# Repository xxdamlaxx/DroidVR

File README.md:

# 🥽 DroidVR

A DIY VR controller ecosystem — open-source hardware and firmware for SteamVR-compatible motion controllers.

---

## License

DroidVR is available under a **dual license** model. Pick whichever fits your use case.

### Option 1 — Free & Open (Attribution Required)

Use, modify, distribute, and sell DroidVR for free, as long as you provide clear and visible attribution in your project's documentation, about page, and repository.

**Required attribution:**

> Built with **DroidVR** by [xxdamlaxx](https://github.com/xxdamlaxx)

See [`LICENSE.md`](LICENSE.md) for full terms.

### Option 2 — Commercial License (No Attribution)

If you prefer not to include attribution, you can purchase a commercial license:

| Tier | Monthly Fee |
|---|---|
| Public / Open-Source Development | $500 / month |
| Private / Closed-Source Development | $5,000 / month |

- Prices may be adjusted at the end of each calendar year.
- No refunds.

See [`LICENSE-COMMERCIAL.md`](LICENSE-COMMERCIAL.md) for full terms.

---

## Contact

For commercial licensing inquiries, reach out via [GitHub](https://github.com/xxdamlaxx) or email *(coming soon)*.

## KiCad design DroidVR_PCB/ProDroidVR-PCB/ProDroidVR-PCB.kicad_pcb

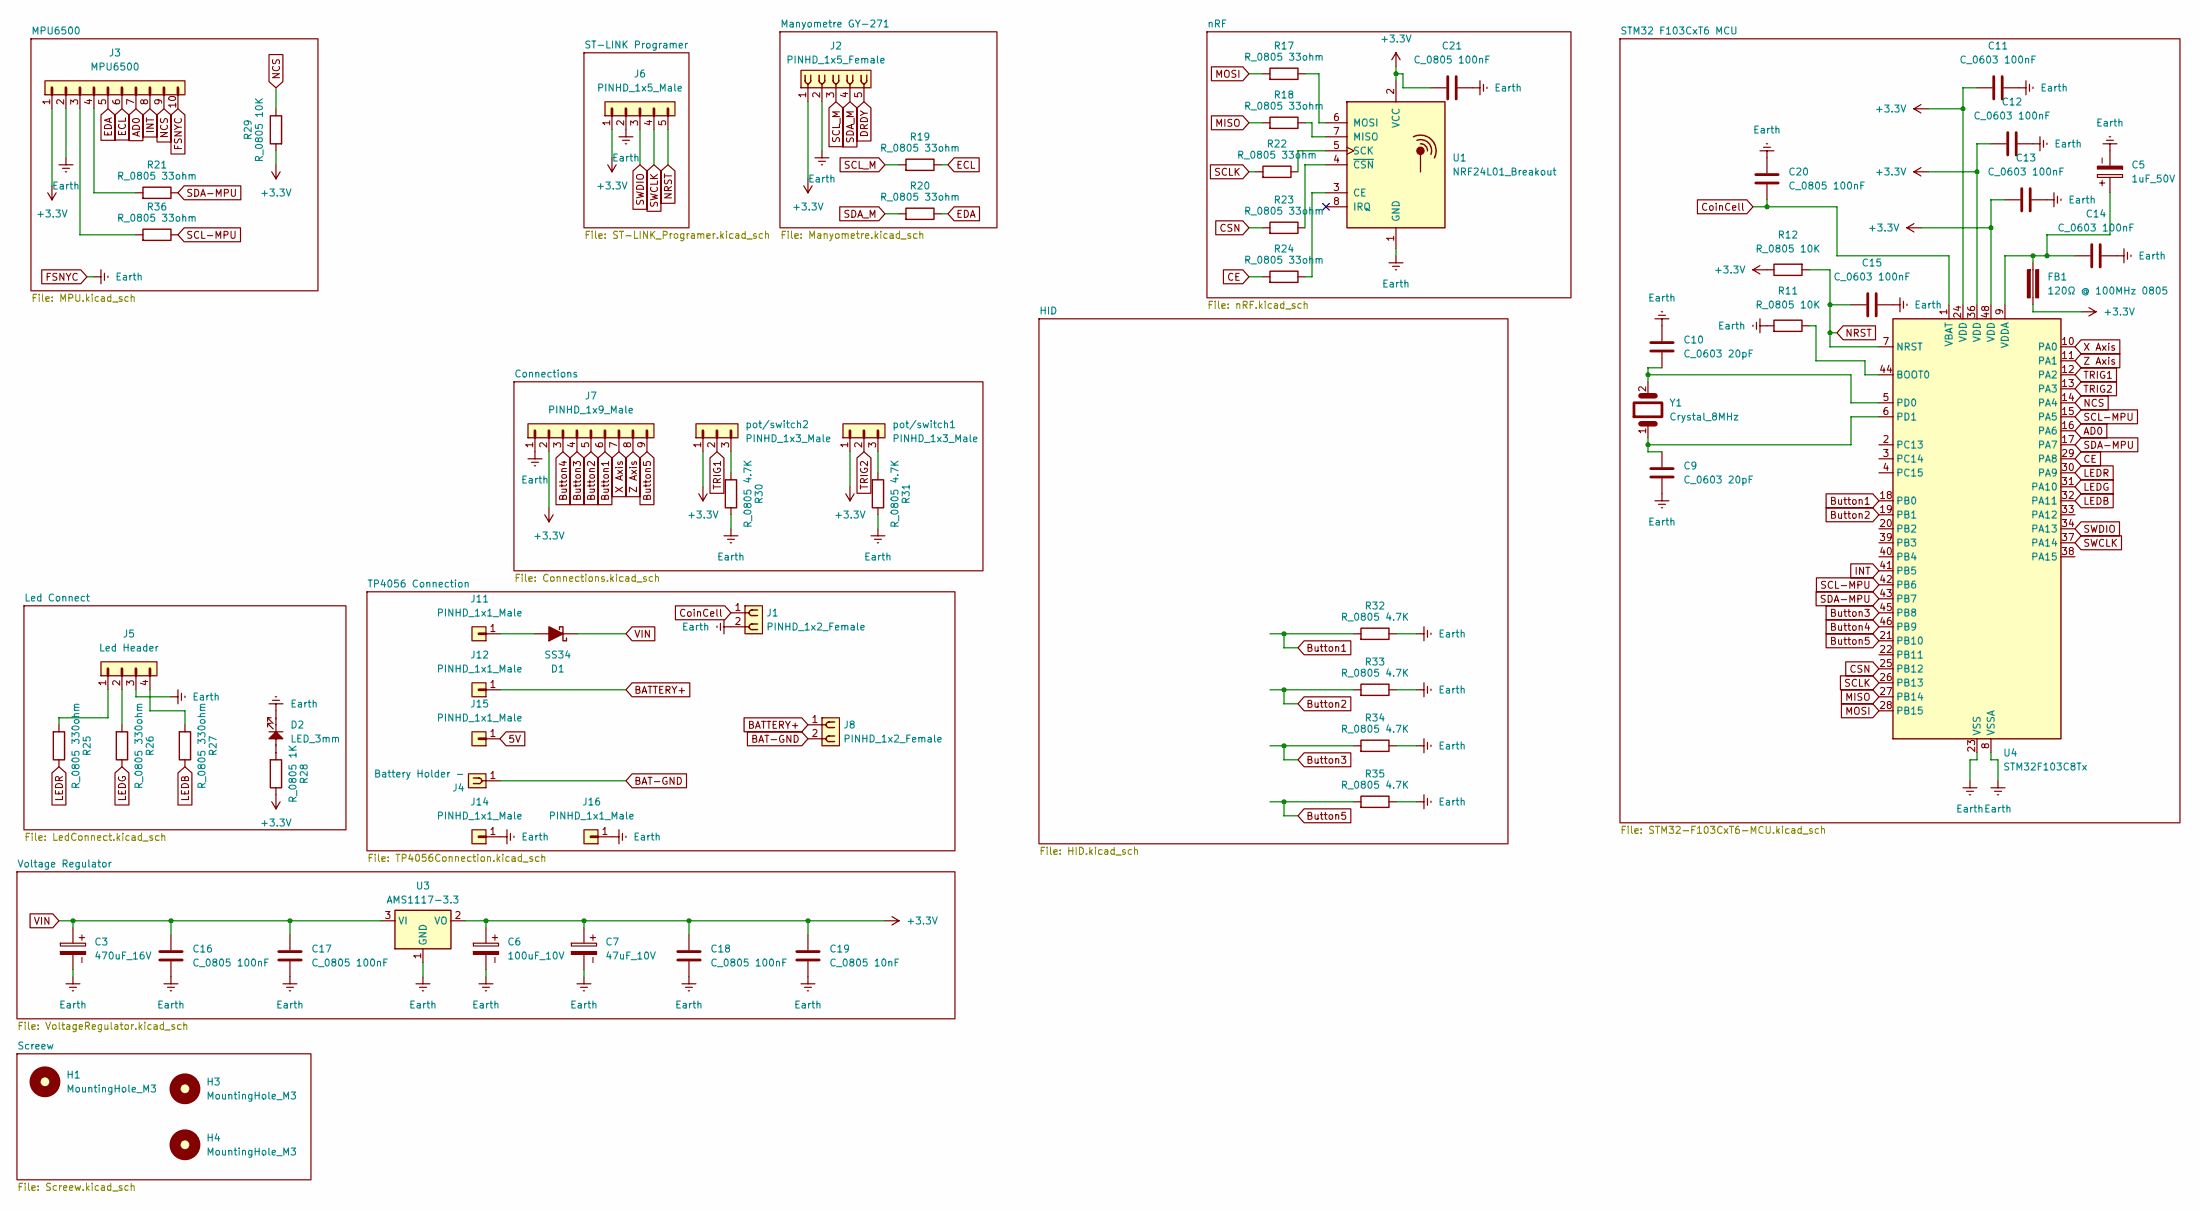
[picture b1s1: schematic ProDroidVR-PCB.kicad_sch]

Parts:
C3: 470uF_16V; CP_Radial_D8.0mm_P3.50mm
C5: 1uF_50V; CP_Radial_D4.0mm_P1.50mm
C6: 100uF_10V; CP_Radial_D5.0mm_P2.00mm
C7: 47uF_10V; CP_Radial_D4.0mm_P1.50mm
C9, C10: C_0603 20pF; C_0603_1608Metric
C11, C12, C13, C14, C15: C_0603 100nF; C_0603_1608Metric
C16, C17, C18, C20, C21: C_0805 100nF; C_0805_2012Metric
C19: C_0805 10nF; C_0805_2012Metric
D1: SS34; D_SMC
D2: LED_3mm; LED_D3.0mm
FB1: 120Ω @ 100MHz 0805; R_0805_2012Metric
H1, H3, H4: MountingHole_M3; MountingHole_3.2mm_M3
J1: PINHD_1x2_Female; BatteryHolder_MYOUNG_BS-07-A1BJ001_CR2032
J2: PINHD_1x5_Female; PinSocket_1x05_P2.54mm_Vertical
J3: MPU6500; PinHeader_1x10_P2.54mm_Vertical
J4: Battery Holder -; TestPoint_THTPad_2.0x2.0mm_Drill1.0mm
J5: Led Header; PinHeader_1x04_P2.54mm_Vertical
J6: PINHD_1x5_Male; PinHeader_1x05_P2.54mm_Vertical
J7: PINHD_1x9_Male; PinHeader_1x09_P2.54mm_Vertical
J8: PINHD_1x2_Female; BatteryHolder_MPD_BH-18650-PC2
J11, J12, J14, J15, J16: PINHD_1x1_Male; TestPoint_THTPad_2.0x2.0mm_Drill1.0mm
R11, R12, R29: R_0805 10K; R_0805_2012Metric
R17, R18, R19, R20, R21, R22, R23, R24, R36: R_0805 33ohm; R_0805_2012Metric
R25, R26, R27: R_0805 330ohm; R_0805_2012Metric
R28: R_0805 1K; R_0805_2012Metric
R30, R31, R32, R33, R34, R35: R_0805 4.7K; R_0805_2012Metric
U1: NRF24L01_Breakout; nRF24L01_Breakout
U3: AMS1117-3.3; SOT-223-3_TabPin2
U4: STM32F103C8Tx; LQFP-48_7x7mm_P0.5mm
Y1: Crystal_8MHz; Crystal_HC49-4H_Vertical
pot/switch1, pot/switch2: PINHD_1x3_Male; PinHeader_1x03_P2.54mm_Vertical

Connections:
5V: J15.1
+3.3V: C6.1, C7.1, C11.1, C12.1, C13.1, C18.2, C19.2, C21.2, FB1.2, J2.1, J3.1, J6.1, J7.2, R12.2, R28.2, R29.1, U1.2 (VCC), U3.2 (VO), U4.24 (VDD), U4.36 (VDD), U4.48 (VDD), pot/switch1.1, pot/switch2.1
AD0: J3.7, U4.16 (PA6)
BAT-GND: J4.1, J8.2
BATTERY+: J8.1, J12.1
Button1: J7.6, R32.1, U4.18 (PB0)
Button2: J7.5, R33.1, U4.19 (PB1)
Button3: J7.4, R34.1, U4.45 (PB8)
Button4: J7.3, U4.46 (PB9)
Button5: J7.9, R35.1, U4.21 (PB10)
CE: R24.1, U4.29 (PA8)
CSN: R23.1, U4.25 (PB12)
CoinCell: C20.2, J1.1, U4.1 (VBAT)
DRDY: J2.5
ECL: J3.6, R19.2
EDA: J3.5, R20.2
FSNYC: C3.2, C5.2, C6.2, C7.2, C9.2, C10.1, C11.2, C12.2, C13.2, C14.2, C15.2, C16.1, C17.1, C18.1, C19.1, C20.1, C21.1, D2.1, J1.2, J2.2, J3.2, J3.10, J5.3, J6.2, J7.1, J14.1, J16.1, R11.1, R30.2, R31.2, R32.2, R33.2, R34.2, R35.2, U1.1 (GND), U3.1 (GND), U4.8 (VSSA), U4.23 (VSS), U4.35 (VSS), U4.47 (VSS)
INT: J3.8, U4.41 (PB5)
LEDB: R27.2, U4.32 (PA11)
LEDG: R26.2, U4.31 (PA10)
LEDR: R25.2, U4.30 (PA9)
MISO: R18.1, U4.27 (PB14)
MOSI: R17.1, U4.28 (PB15)
NCS: J3.9, R29.2, U4.14 (PA4)
NRST: C15.1, J6.5, R12.1, U4.7 (NRST)
unnamed: D1.2 (A), J11.1
unnamed: D2.2, R28.1
unnamed: J3.3, R36.1
unnamed: J3.4, R21.1
unnamed: J5.1, R25.1
unnamed: J5.2, R26.1
unnamed: J5.4, R27.1
unnamed: R30.1, pot/switch2.3
unnamed: R31.1, pot/switch1.3
unnamed: R24.2, U1.3 (CE)
unnamed: R18.2, U1.7 (MISO)
unnamed: R17.2, U1.6 (MOSI)
unnamed: R22.2, U1.5 (SCK)
unnamed: R23.2, U1.4 (~CSN)
unnamed: R11.2, U4.44 (BOOT0)
unnamed: C10.2, U4.5 (PD0), Y1.2
unnamed: C9.1, U4.6 (PD1), Y1.1
unnamed: C5.1, C14.1, FB1.1, U4.9 (VDDA)
SCL-MPU: R36.2, U4.15 (PA5), U4.42 (PB6)
SCLK: R22.1, U4.26 (PB13)
SCL_M: J2.3, R19.1
SDA-MPU: R21.2, U4.17 (PA7), U4.43 (PB7)
SDA_M: J2.4, R20.1
SWCLK: J6.4, U4.37 (PA14)
SWDIO: J6.3, U4.34 (PA13)
TRIG1: U4.12 (PA2), pot/switch2.2
TRIG2: U4.13 (PA3), pot/switch1.2
VIN: C3.1, C16.2, C17.2, D1.1 (K), U3.3 (VI)
X Axis: J7.7, U4.10 (PA0)
Z Axis: J7.8, U4.11 (PA1)

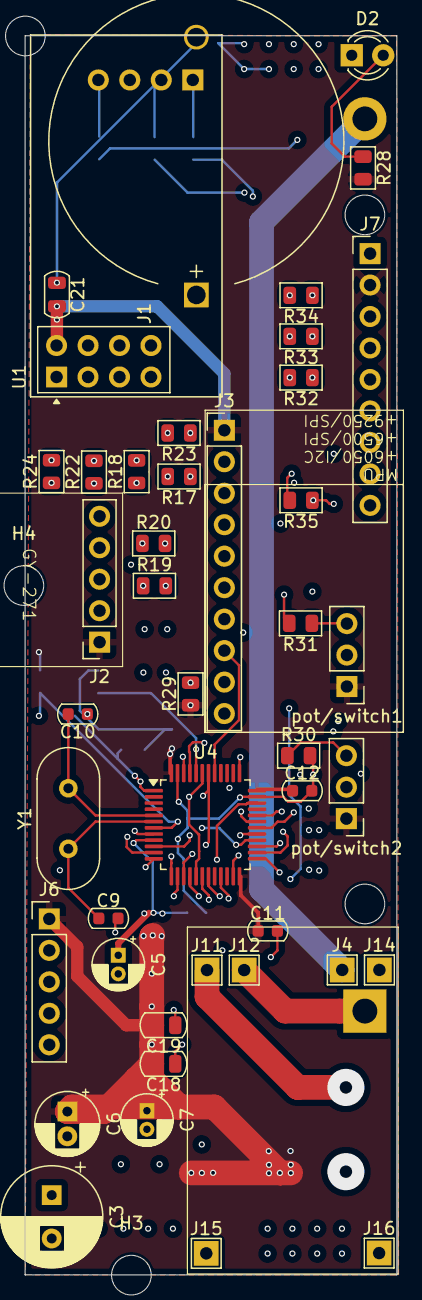
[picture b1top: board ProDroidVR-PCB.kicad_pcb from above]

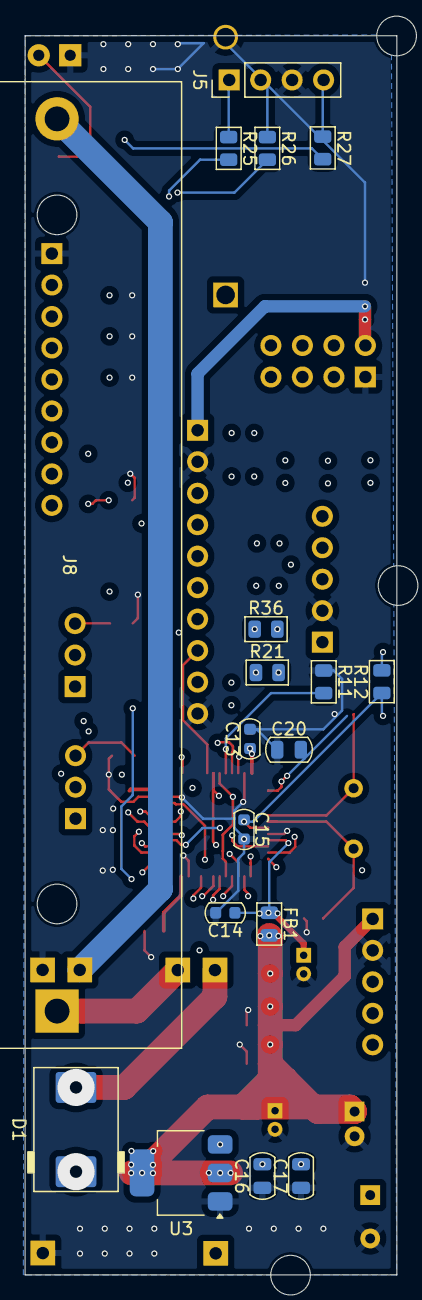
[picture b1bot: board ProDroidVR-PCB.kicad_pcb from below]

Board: 4 copper layers, 30.0 x 100.0 mm, 64 parts (18 on the bottom side), 53 nets.

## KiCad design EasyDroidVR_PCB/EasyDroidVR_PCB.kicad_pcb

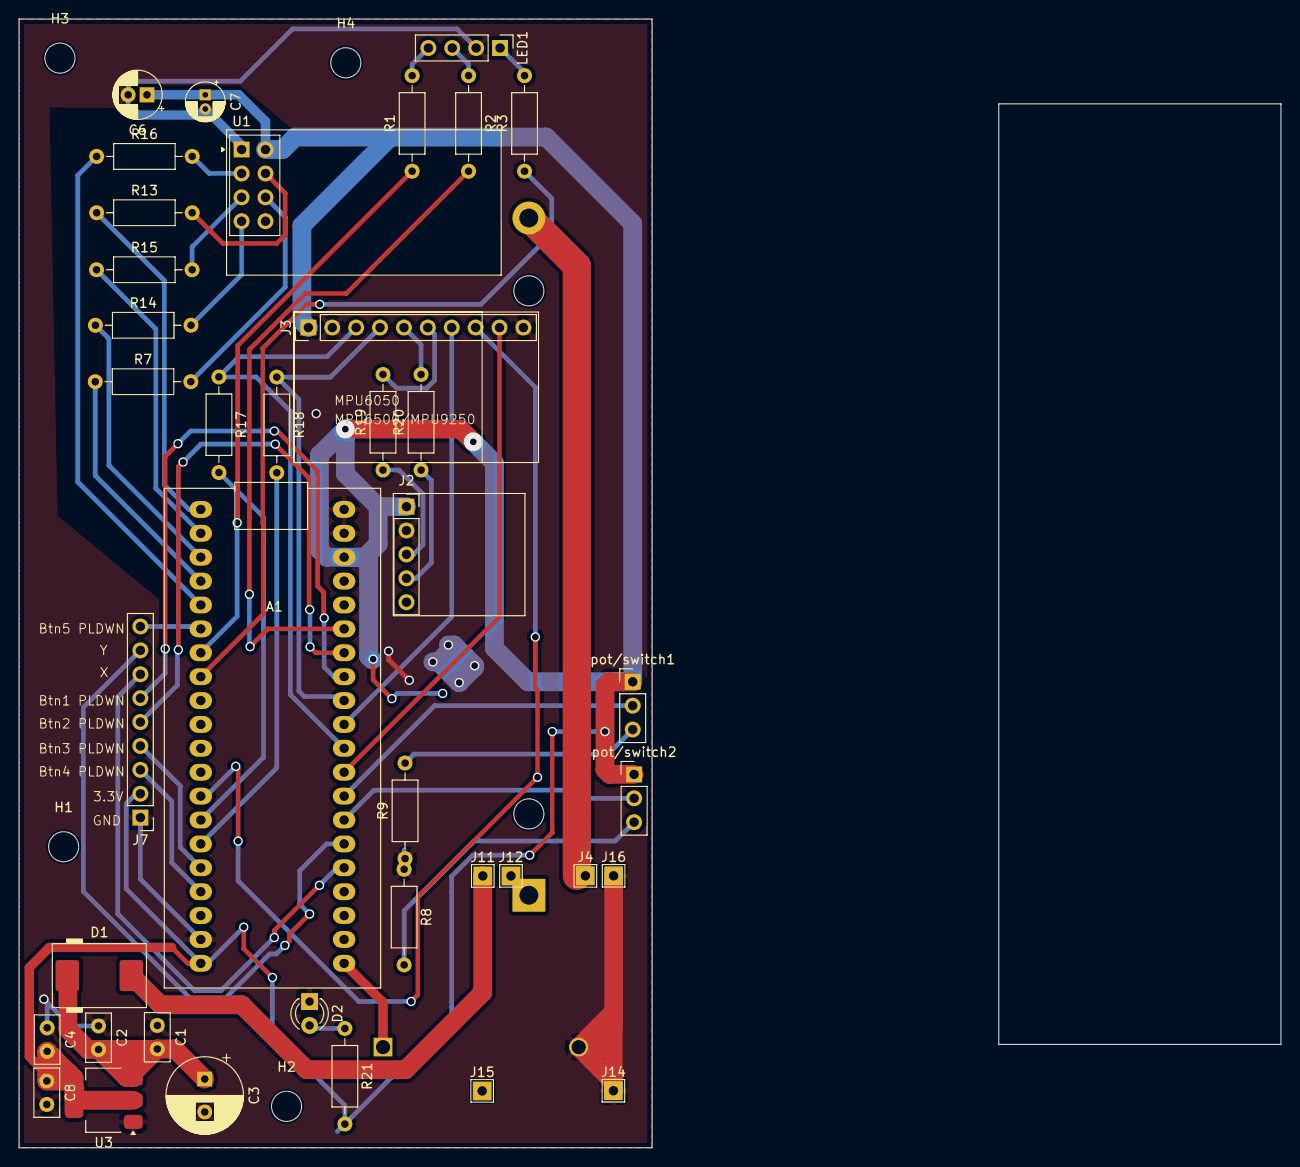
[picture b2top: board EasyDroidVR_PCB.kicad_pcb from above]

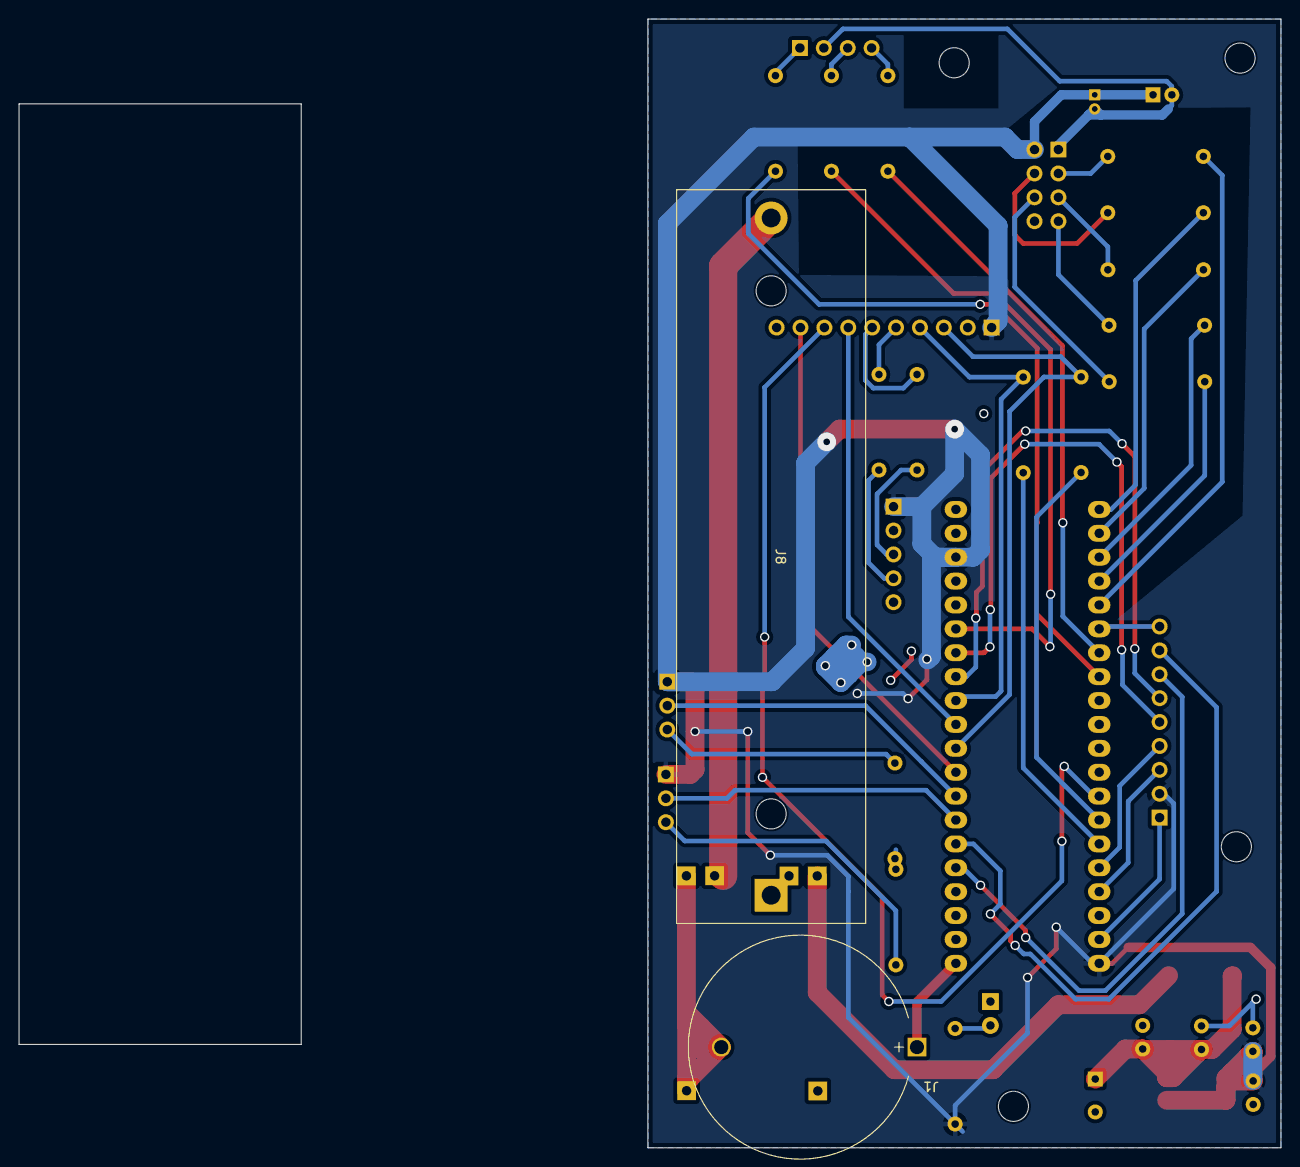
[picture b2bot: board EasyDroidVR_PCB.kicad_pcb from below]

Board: 2 copper layers, 67.3 x 120.0 mm, 45 parts (2 on the bottom side), 46 nets.

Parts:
A1: STM32_Blue_Pill_DevBoard
C1, C2, C4: 100nF_Ceramic; C_Disc_D5.0mm_W2.5mm_P2.50mm
C3: 470uF_16V; CP_Radial_D8.0mm_P3.50mm
C6: 100uF_10V; CP_Radial_D5.0mm_P2.00mm
C7: 47uF_10V; CP_Radial_D4.0mm_P1.50mm
C8: 10nF_Ceramic; C_Disc_D5.0mm_W2.5mm_P2.50mm
D1: SS34; D_SMC
D2: LED_3mm; LED_D3.0mm
H1, H2, H3, H4: MountingHole_M3; MountingHole_3.2mm_M3
J1: PINHD_1x2_Female; BatteryHolder_MYOUNG_BS-07-A1BJ001_CR2032
J2: PINHD_1x5_Female; PinSocket_1x05_P2.54mm_Vertical
J3: MPU6500; PinHeader_1x10_P2.54mm_Vertical
J4: Battery Holder -; TestPoint_THTPad_2.0x2.0mm_Drill1.0mm
J7: PINHD_1x9_Male; PinHeader_1x09_P2.54mm_Vertical
J8: PINHD_1x2_Female; BatteryHolder_MPD_BH-18650-PC2
J11, J12, J14, J15, J16: PINHD_1x1_Male; TestPoint_THTPad_2.0x2.0mm_Drill1.0mm
LED1: LED_5mm_RGB_Kcom_BKRG; PinHeader_1x04_P2.54mm_Vertical
R1, R2, R3: 330ohm; R_Axial_DIN0207_L6.3mm_D2.5mm_P10.16mm_Horizontal
R7, R13, R14, R15, R16, R17, R18, R19, R20: 33ohm; R_Axial_DIN0207_L6.3mm_D2.5mm_P10.16mm_Horizontal
R8, R9: 4.7k; R_Axial_DIN0207_L6.3mm_D2.5mm_P10.16mm_Horizontal
R21: 1k; R_Axial_DIN0207_L6.3mm_D2.5mm_P10.16mm_Horizontal
U1: NRF24L01_Breakout; nRF24L01_Breakout
U3: AMS1117-3.3; SOT-223-3_TabPin2
pot/switch1, pot/switch2: PINHD_1x3_Male; PinHeader_1x03_P2.54mm_Vertical

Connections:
+3.3V: A1.20 (3V3), A1.38 (3V3), C4.2, C6.1, C7.1, C8.1, J2.1, J3.1, J7.2, R21.2, U1.2 (VCC), U3.2 (VO), pot/switch1.1, pot/switch2.1
AD0: A1.31 (MISO1/PA6), J3.7
BAT-GND: J4.1, J8.2
BATTERY+: J8.1, J12.1
Button1: A1.33 (PB0), J7.6
Button2: A1.34 (PB1), J7.5
Button3: A1.16 (PB8/SCL1), J7.4
Button4: A1.17 (PB9/SDA1), J7.3
Button5: A1.6 (PA9/TX1), J7.9
CE: A1.5 (PA8/CK1), R16.1
CSN: A1.1 (PB12/NSS2), R13.1
CoinCell: A1.21 (VBAT), J1.1
ECL: J3.6, R19.2
EDA: J3.5, R20.2
FSNYC: A1.19 (GND), A1.39 (GND), A1.40 (GND), C1.1, C2.1, C3.2, C4.1, C6.2, C7.2, C8.2, D2.1, J1.2, J2.2, J3.2, J3.10, J7.1, J14.1, J16.1, LED1.2 (A), R8.1, R9.1, U1.1 (GND), U3.1 (GND)
INT: A1.13 (PB5/MOSI1), J3.8
LEDB: A1.8 (PA11/~USB-), R3.1
LEDG: A1.7 (PA10/RX1), R1.1
LEDR: A1.35 (SCL2/TX3/PB10), R2.2
MISO: A1.3 (PB14/MISO2), R14.1
MOSI: A1.4 (PB15/MOSI2), R7.1
NCS: A1.29 (NSS1/PA4), J3.9
unnamed: A1.14 (PB6/SCL1/TX1), R17.2
unnamed: A1.15 (PB7/SDA1/RX1), R18.2
unnamed: D1.2 (A), J11.1
unnamed: D2.2, R21.1
unnamed: LED1.1 (B), R3.2
unnamed: LED1.4 (G), R1.2
unnamed: LED1.3 (R), R2.1
unnamed: R8.2, pot/switch2.3
unnamed: R9.2, pot/switch1.3
unnamed: R16.2, U1.3 (CE)
unnamed: R14.2, U1.7 (MISO)
unnamed: R7.2, U1.6 (MOSI)
unnamed: R15.2, U1.5 (SCK)
unnamed: R13.2, U1.4 (~CSN)
SCL: A1.30 (SCK1/PA5), J3.3, R17.1
SCLK: A1.2 (PB13/SCK2), R15.1
SCL_M: J2.3, R19.1
SDA: A1.32 (MOSI1/PA7), J3.4, R18.1
SDA_M: J2.4, R20.1
TRIG1: A1.27 (TX2/PA2), pot/switch2.2
TRIG2: A1.28 (RX2/PA3), pot/switch1.2
VIN: C1.2, C2.2, C3.1, D1.1 (K), U3.3 (VI)
X Axis: A1.25 (PA0), J7.7
Z Axis: A1.26 (PA1), J7.8

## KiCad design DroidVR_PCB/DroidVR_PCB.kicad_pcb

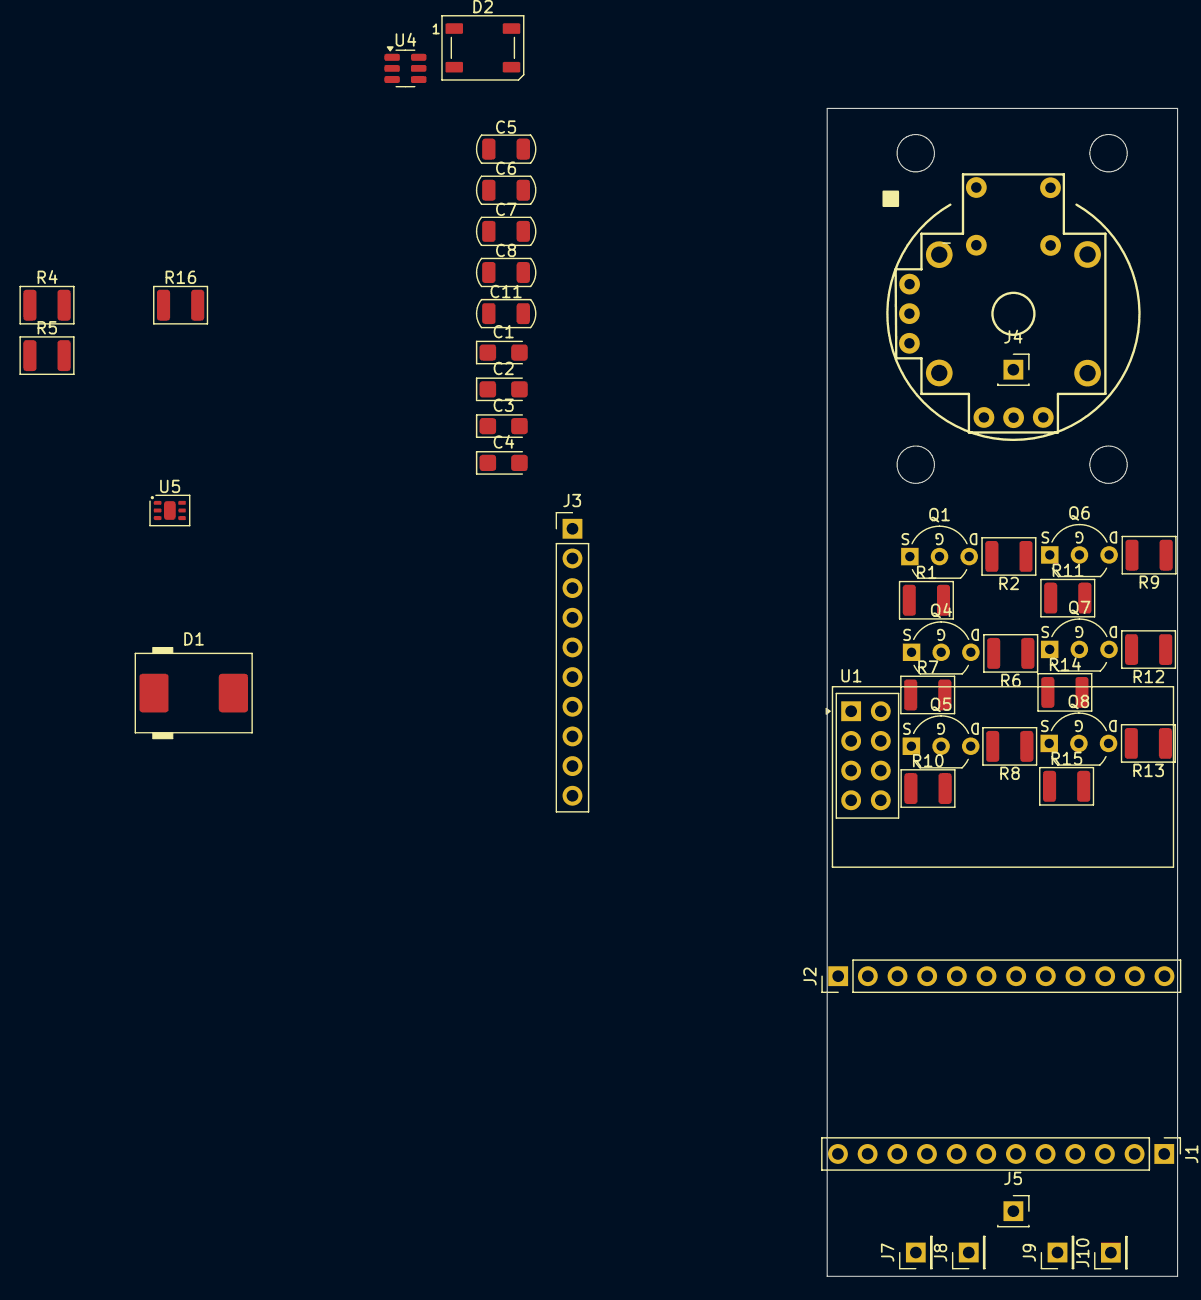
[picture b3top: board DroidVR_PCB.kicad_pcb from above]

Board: 2 copper layers, 30.0 x 100.0 mm, 49 parts (0 on the bottom side), 20 nets, no tracks yet.

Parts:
C1: C_Polarized 10uF/10V+; CP_EIA-3216-18_Kemet-A
C2: C_Polarized 10uF/16V+; CP_EIA-3216-18_Kemet-A
C3: C_Polarized 22uF/6.3V+; CP_EIA-3216-18_Kemet-A
C4: C_Polarized 22uF/10V+; CP_EIA-3216-18_Kemet-A
C5, C6, C7, C8, C11: C_1206 100nF; C_1206_3216Metric
D1: SS34; D_SMC
D2: WS2812B; LED_WS2812B_PLCC4_5.0x5.0mm_P3.2mm
H1, H2, H3, H4: MountingHole; MountingHole_3.2mm_M3_DIN965
J1, J2: PINHD_1x12_Male; PinHeader_1x12_P2.54mm_Vertical
J3: MPU6500; PinHeader_1x10_P2.54mm_Vertical
J4: Battery Holder -; PinSocket_1x01_P2.54mm_Vertical
J5: Battery Holder +; PinSocket_1x01_P2.54mm_Vertical
J7, J8, J9, J10: PINHD_1x1_Male; PinHeader_1x01_P2.54mm_Vertical
Q1, Q4, Q5, Q6, Q7, Q8: 2N7000; TO-92_Inline_Wide_SGD
R1, R2, R6, R7, R8, R9, R10, R11, R12, R13, R14, R15: R_1210 4.7KOhm; R_1210_3225Metric
R4, R5: R_1210 5.1KOhm; R_1210_3225Metric
R16: R_1210 330Ohm; R_1210_3225Metric
U1: COM-09032; XDCR_COM-09032
U1#2: NRF24L01_Breakout; nRF24L01_Breakout
U4: MT3608; SOT-23-6
U5: MCP1700T-3002E-MAY; DFN-6-1EP_2x2mm_P0.65mm_EP1x1.6mm

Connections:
+3.3V: C1.1, C3.1, J3.1, Q1.2 (G), Q4.2 (G), Q5.2 (G), Q6.2 (G), Q7.2 (G), Q8.2 (G), R1.2, R7.2, R10.2, R11.2, R14.2, R15.2, U1#2.2 (VCC), U5.6 (OUT)
+5V: C2.1, C4.1, C7.1, C8.1, D2.1 (VDD), J2.9, R2.1, R6.1, R9.1, R12.1, R13.1, U1.B1A (SEL+), U1.H1 (H+), U1.V1 (V+), U5.1 (IN)
A8: J3.9, Q8.1 (S), R15.1
A8_A: J1.11, Q8.3 (D), R13.2
A9: Q7.1 (S), R14.1, U1#2.3 (CE)
A9_A: J1.12, Q7.3 (D), R12.2
A10: Q6.1 (S), R11.1, U1#2.4 (~CSN)
A10_A: J2.1, Q6.3 (D), R9.2
AmperMater: C1.2, C2.2, C3.2, C4.2, C5.2, C6.2, C7.2, C8.2, C11.1, D2.3 (VSS), J1.3, J1.4, J2.11, J3.2, J3.10, R4.1, R5.1, U1#2.1 (GND), U4.2 (GND), U5.3, U5.7
Li-ion: D1.2 (A), J5.1
MISO: J3.7, Q4.1 (S), R7.1, U1#2.7 (MISO)
MISO_A: J2.3, Q4.3 (D), R6.2
MOSI: J3.4, Q5.1 (S), R10.1, U1#2.6 (MOSI)
MOSI_A: J2.2, Q5.3 (D), R8.2
unnamed: D2.4 (DIN), R16.1
unnamed: U1.S1 (SHIELD), U1.S2 (SHIELD), U1.S3 (SHIELD), U1.S4 (SHIELD)
SCLK: J3.3, Q1.1 (S), R1.1, U1#2.5 (SCK)
SCLK_A: J2.4, Q1.3 (D), R2.2
TX: J1.1, R16.2
VIN: C5.1, C6.1, D1.1 (K), U4.4 (EN), U4.5 (IN)

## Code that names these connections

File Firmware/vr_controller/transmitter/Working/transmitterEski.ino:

/*
 * DIY VR Sağ Kol - Verici (BluePill STM32F103C8T6)
 * 
 * Bağlantılar:
 *   MPU6500 (I2C1): SCL→PB6, SDA→PB7, VCC→3.3V, GND→GND
 *   NRF24L01 (SPI1): SCK→PA5, MISO→PA6, MOSI→PA7, CSN→PA4, CE→PB0
 *   Joystick: VRx→PA0, VRy→PA1, SW→PB10
 *   Tetik pot (20K): Signal→PA3
 * 
 * Board: Generic STM32F1 series → BluePill F103C8
 * Upload: STLink veya Serial
 * Kütüphane: RF24 by TMRh20
 */

#include <Wire.h>
#include <SPI.h>
#include <RF24.h>

// ===== PINLER =====
#define NRF_CE   PB0
#define NRF_CSN  PA4
#define JOY_X    PA0
#define JOY_Y    PA1
#define JOY_SW   PB10
#define TRIGGER  PA3

// ===== NRF24 =====
RF24 radio(NRF_CE, NRF_CSN);
const uint64_t pipe = 0xF0F0F0F0E1LL;

// ===== MPU =====
#define MPU_ADDR     0x68
#define WHO_AM_I     0x75
#define PWR_MGMT_1   0x6B
#define CONFIG_REG   0x1A
#define GYRO_CONFIG  0x1B
#define ACCEL_CONFIG 0x1C
#define ACCEL_XOUT_H 0x3B

// ===== QUATERNION =====
float qw = 1, qx = 0, qy = 0, qz = 0;
float gxOff = 0, gyOff = 0, gzOff = 0;
unsigned long lastTime = 0;

// ===== PAKET =====
struct __attribute__((packed)) Packet {
  float qw, qx, qy, qz;
  int16_t joyX, joyY;
  int16_t trigger;
  uint8_t buttons;
};

Packet pkt;

// ===== MPU FONKSIYONLARI =====
void mpuWrite(uint8_t reg, uint8_t val) {
  Wire.beginTransmission(MPU_ADDR);
  Wire.write(reg);
  Wire.write(val);
  Wire.endTransmission();
}

uint8_t mpuRead(uint8_t reg) {
  Wire.beginTransmission(MPU_ADDR);
  Wire.write(reg);
  Wire.endTransmission(false);
  Wire.requestFrom(MPU_ADDR, (uint8_t)1);
  return Wire.read();
}

void mpuReadBytes(uint8_t reg, uint8_t* buf, uint8_t len) {
  Wire.beginTransmission(MPU_ADDR);
  Wire.write(reg);
  Wire.endTransmission(false);
  Wire.requestFrom(MPU_ADDR, len);
  for (uint8_t i = 0; i < len; i++) buf[i] = Wire.read();
}

bool initMPU() {
  mpuWrite(PWR_MGMT_1, 0x80); // reset
  delay(100);

  uint8_t id = mpuRead(WHO_AM_I);
  Serial.print("WHO_AM_I: 0x");
  Serial.println(id, HEX);

  if (id == 0x70 || id == 0x71) Serial.println("MPU6500 OK");
  else if (id == 0x68) Serial.println("MPU6050 OK");
  else {
    Serial.println("MPU BULUNAMADI! Sahte modul olabilir.");
    return false;
  }

  mpuWrite(PWR_MGMT_1, 0x01); // PLL clock
  delay(10);
  mpuWrite(0x6C, 0x00);       // tum eksenler aktif
  mpuWrite(CONFIG_REG, 0x04); // DLPF 20Hz
  mpuWrite(GYRO_CONFIG, 0x08); // +-500 derece/s
  mpuWrite(ACCEL_CONFIG, 0x08); // +-4g
  return true;
}

void calibrateGyro() {
  Serial.print("Gyro kalibrasyonu");
  float sx = 0, sy = 0, sz = 0;
  for (int i = 0; i < 500; i++) {
    uint8_t buf[6];
    mpuReadBytes(0x43, buf, 6);
    sx += (int16_t)(buf[0] << 8 | buf[1]);
    sy += (int16_t)(buf[2] << 8 | buf[3]);
    sz += (int16_t)(buf[4] << 8 | buf[5]);
    delay(2);
    if (i % 100 == 0) Serial.print(".");
  }
  gxOff = sx / 500.0f;
  gyOff = sy / 500.0f;
  gzOff = sz / 500.0f;
  Serial.println(" OK");
}

// ===== MADGWICK =====
void madgwick(float gx, float gy, float gz, float ax, float ay, float az, float dt) {
  float beta = 0.1f;
  float q0 = qw, q1 = qx, q2 = qy, q3 = qz;

  float norm = sqrtf(ax*ax + ay*ay + az*az);
  if (norm < 0.001f) return;
  ax /= norm; ay /= norm; az /= norm;

  float _2q0 = 2*q0, _2q1 = 2*q1, _2q2 = 2*q2, _2q3 = 2*q3;
  float _4q0 = 4*q0, _4q1 = 4*q1, _4q2 = 4*q2;
  float _8q1 = 8*q1, _8q2 = 8*q2;
  float q0q0 = q0*q0, q1q1 = q1*q1, q2q2 = q2*q2, q3q3 = q3*q3;

  float s0 = _4q0*q2q2 + _2q2*ax + _4q0*q1q1 - _2q1*ay;
  float s1 = _4q1*q3q3 - _2q3*ax + 4*q0q0*q1 - _2q0*ay - _4q1 + _8q1*q1q1 + _8q1*q2q2 + _4q1*az;
  float s2 = 4*q0q0*q2 + _2q0*ax + _4q2*q3q3 - _2q3*ay - _4q2 + _8q2*q1q1 + _8q2*q2q2 + _4q2*az;
  float s3 = 4*q1q1*q3 - _2q1*ax + 4*q2q2*q3 - _2q2*ay;

  norm = sqrtf(s0*s0 + s1*s1 + s2*s2 + s3*s3);
  if (norm < 0.001f) return;
  s0 /= norm; s1 /= norm; s2 /= norm; s3 /= norm;

  float qDot0 = 0.5f*(-q1*gx - q2*gy - q3*gz);
  float qDot1 = 0.5f*( q0*gx + q2*gz - q3*gy);
  float qDot2 = 0.5f*( q0*gy - q1*gz + q3*gx);
  float qDot3 = 0.5f*( q0*gz + q1*gy - q2*gx);

  q0 += (qDot0 - beta*s0)*dt;
  q1 += (qDot1 - beta*s1)*dt;
  q2 += (qDot2 - beta*s2)*dt;
  q3 += (qDot3 - beta*s3)*dt;

  norm = sqrtf(q0*q0 + q1*q1 + q2*q2 + q3*q3);
  qw = q0/norm; qx = q1/norm; qy = q2/norm; qz = q3/norm;
}

// ===== SETUP =====
void setup() {
  Serial.begin(115200);
  delay(500);
  Serial.println("=== VR Verici Basliyor ===");

  pinMode(JOY_SW, INPUT_PULLUP);

  // I2C
  Wire.begin();
  Wire.setClock(400000);

  // MPU
  if (!initMPU()) {
    Serial.println("MPU HATA! Durduruluyor.");
    while (1) delay(1000);
  }
  calibrateGyro();

  // NRF24
  Serial.print("NRF24 baslatiliyor... ");
  if (!radio.begin()) {
    Serial.println("BASARISIZ!");
    while (1) delay(1000);
  }
  Serial.println("OK");

  radio.setPALevel(RF24_PA_HIGH);
  radio.setDataRate(RF24_1MBPS);
  radio.setChannel(76);
  radio.setPayloadSize(sizeof(Packet));
  radio.setRetries(3, 5);
  radio.openWritingPipe(pipe);
  radio.stopListening();

  // NRF24 detaylari
  Serial.print("Payload: "); Serial.println(sizeof(Packet));
  Serial.print("Kanal: "); Serial.println(radio.getChannel());
  Serial.println("=== Verici Hazir ===");
  lastTime = micros();
}

// ===== LOOP =====
unsigned long lastPrint = 0;
int okCount = 0, failCount = 0;

void loop() {
  unsigned long now = micros();
  float dt = (now - lastTime) / 1000000.0f;
  lastTime = now;

  // MPU oku
  uint8_t raw[14];
  mpuReadBytes(ACCEL_XOUT_H, raw, 14);

  float ax = (int16_t)(raw[0]<<8|raw[1]) / 8192.0f;
  float ay = (int16_t)(raw[2]<<8|raw[3]) / 8192.0f;
  float az = (int16_t)(raw[4]<<8|raw[5]) / 8192.0f;

  float gx = ((int16_t)(raw[8]<<8|raw[9])  - gxOff) / 65.5f * DEG_TO_RAD;
  float gy = ((int16_t)(raw[10]<<8|raw[11]) - gyOff) / 65.5f * DEG_TO_RAD;
  float gz = ((int16_t)(raw[12]<<8|raw[13]) - gzOff) / 65.5f * DEG_TO_RAD;

  madgwick(gx, gy, gz, ax, ay, az, dt);

  // Joystick
  pkt.joyX = map(analogRead(JOY_X), 0, 4095, -512, 512);
  pkt.joyY = map(analogRead(JOY_Y), 0, 4095, -512, 512);

  // Tetik
  pkt.trigger = map(analogRead(TRIGGER), 0, 4095, 0, 1000);

  // Butonlar
  pkt.buttons = 0;
  if (digitalRead(JOY_SW) == LOW) pkt.buttons |= 0x01;

  // Quaternion
  pkt.qw = qw;
  pkt.qx = qx;
  pkt.qy = qy;
  pkt.qz = qz;

  // Gonder
  bool ok = radio.write(&pkt, sizeof(pkt));
  if (ok) okCount++; else failCount++;

  // Her 2 saniyede durum yazdir
  if (millis() - lastPrint > 2000) {
    Serial.print("OK:"); Serial.print(okCount);
    Serial.print(" FAIL:"); Serial.print(failCount);
    Serial.print(" Q:"); Serial.print(qw,2);
    Serial.print(","); Serial.print(qx,2);
    Serial.print(","); Serial.print(qy,2);
    Serial.print(","); Serial.print(qz,2);
    Serial.print(" J:"); Serial.print(pkt.joyX);
    Serial.print(","); Serial.print(pkt.joyY);
    Serial.print(" T:"); Serial.println(pkt.trigger);
    okCount = 0;
    failCount = 0;
    lastPrint = millis();
  }

  delayMicroseconds(5000);
}

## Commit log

2026-03-17 V 0.0.1
2026-04-07 V1.0 Working
